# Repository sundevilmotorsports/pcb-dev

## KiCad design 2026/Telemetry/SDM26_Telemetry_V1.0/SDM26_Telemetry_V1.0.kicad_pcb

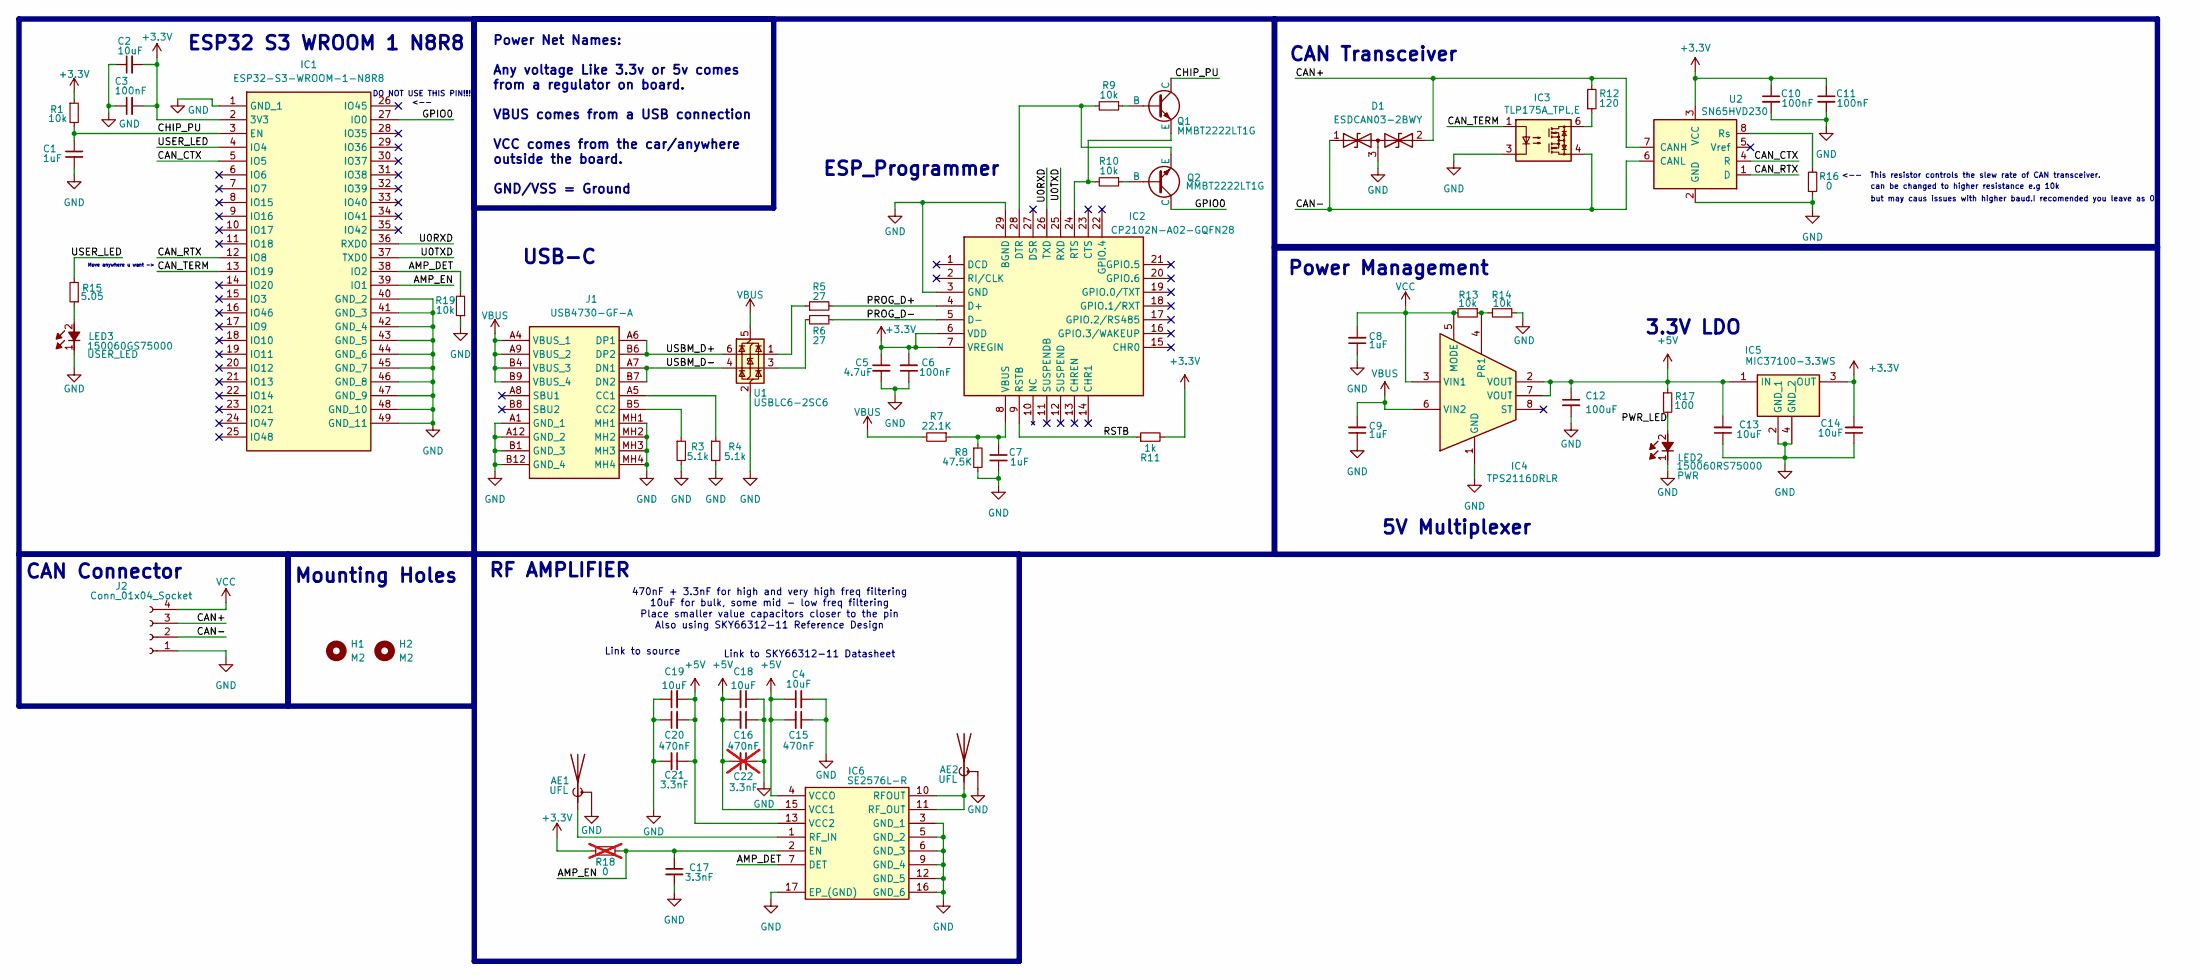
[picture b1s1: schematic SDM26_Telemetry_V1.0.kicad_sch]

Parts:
AE1, AE2: UFL; CONUFL001SMDT; Mouser Part Number N/A
C1, C7, C8, C9: 1uF; C_0603_1608Metric
C2, C4, C13, C14, C18, C19: 10uF; C_0603_1608Metric
C3, C6, C10, C11: 100nF; C_0603_1608Metric
C5: 4.7uF; C_0603_1608Metric
C12: 100uF; C_0603_1608Metric
C15, C16, C20: 470nF; C_0603_1608Metric
C17, C21: 3.3nF; C_0603_1608Metric
C22: 3.3nF; C_0603_1608Metric; not fitted
D1: ESDCAN03-2BWY; SOT65P210X110-3N; Mouser Part Number 511-ESDCAN03-2BWY
H1, H2: M2; MountingHole_2.2mm_M2
IC1: ESP32-S3-WROOM-1-N8R8; ESP32S3WROOM1UN8R8; Mouser Part Number 356-ESP32S3WRM1UN8R8
IC2: CP2102N-A02-GQFN28; QFN50P500X500X80-29N-D; Mouser Part Number 634-CP2102NA02GQFN28
IC3: TLP175A_TPL,E; TLP266J; Mouser Part Number 757-TLP175A(TPLE
IC4: TPS2116DRLR; SOTFL50P160X60-8L; Mouser Part Number 595-TPS2116DRLR
IC5: MIC37100-3.3WS; SOT230P700X180-4N; Mouser Part Number 998-MIC37100-3.3WS
IC6: SE2576L-R; QFN50P300X300X90-17L-D; Mouser Part Number 873-SE2576L-R
J1: USB4730-GF-A; USB_C_Receptacle_16P; Mouser Part Number 640-USB4730GFA
J2: Conn_01x04_Socket; JST_XH_S4B-XH-A_1x04_P2.50mm_Horizontal
LED2: 150060RS75000; LEDC1608X80N; Mouser Part Number 710-150060RS75000
LED3: 150060GS75000; LEDC1608X80N; Mouser Part Number 710-150060GS75000
Q1, Q2: MMBT2222LT1G; SOT96P237X111-3N
R1, R9, R10, R13, R14, R19: 10k; R_0603_1608Metric
R3, R4: 5.1k; R_0603_1608Metric
R5, R6: 27; R_0603_1608Metric
R7: 22.1K; R_0603_1608Metric
R8: 47.5K; R_0603_1608Metric
R11: 1k; R_0603_1608Metric
R12: 120; R_0603_1608Metric
R15: 5.05; R_0603_1608Metric
R16: 0; R_0603_1608Metric
R17: 100; R_0603_1608Metric
R18: 0; R_0603_1608Metric; not fitted
U1: USBLC6-2SC6; SOT-23-6
U2: SN65HVD230; SOIC-8_3.9x4.9mm_P1.27mm

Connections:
+3.3V: C2.2, C3.2, C5.1, C6.2, C10.1, C11.1, C14.2, IC1.2 (3V3), IC2.6 (VDD), IC2.7 (VREGIN), IC5.3 (OUT), R1.1, R11.2, R18.1, U2.3 (VCC)
+5V: C4.1, C12.1, C13.2, C15.2, C16.2, C18.2, C19.2, C20.2, C21.1, C22.2, IC4.2 (VOUT), IC4.7 (VOUT), IC5.1 (IN), IC6.4 (VCCO), IC6.13 (VCC2), IC6.15 (VCC1), R17.1
/AMP_DET: IC1.38 (IO2), IC6.7 (DET), R19.2
/AMP_EN: C17.1, IC1.39 (IO1), IC6.2 (EN), R18.2
/CAN+: D1.2, J2.3, R12.2, U2.7 (CANH)
/CAN-: D1.1, IC3.4, J2.2, U2.6 (CANL)
/CAN_CTX: IC1.5 (IO5), U2.4 (R)
/CAN_RTX: IC1.12 (IO8), U2.1 (D)
/CAN_TERM: IC1.13 (IO19), IC3.1
/CHIP_PU: C1.1, IC1.3 (EN), Q1.3 (C), R1.2
/GPIO0: IC1.27 (IO0), Q2.3 (C)
/PROG_D+: IC2.4 (D+), R5.2
/PROG_D-: IC2.5 (D-), R6.1
/PWR_LED: LED2.2 (A), R17.2
/RSTB: IC2.9 (RSTB), R11.1
/U0RXD: IC1.36 (RXD0), IC2.26 (TXD)
/U0TXD: IC1.37 (TXD0), IC2.25 (RXD)
/USBM_D+: J1.A6 (DP1), J1.B6 (DP2), U1.6 (I/O1)
/USBM_D-: J1.A7 (DN1), J1.B7 (DN2), U1.4 (I/O2)
/USER_LED: IC1.4 (IO4), R15.2
GND: AE1.2 (Shield), AE1.3 (Shield), AE2.2 (Shield), AE2.3 (Shield), C1.2, C2.1, C3.1, C4.2, C5.2, C6.1, C7.2, C8.1, C9.1, C10.2, C11.2, C12.2, C13.1, C14.1, C15.1, C16.1, C17.2, C18.1, C19.1, C20.1, C21.2, C22.1, D1.3, IC1.1 (GND_1), IC1.40 (GND_2), IC1.41 (GND_3), IC1.42 (GND_4), IC1.43 (GND_5), IC1.44 (GND_6), IC1.45 (GND_7), IC1.46 (GND_8), IC1.47 (GND_9), IC1.48 (GND_10), IC1.49 (GND_11), IC2.3 (GND), IC2.29 (BGND), IC3.3, IC4.1 (GND), IC5.2 (GND_1), IC5.4 (GND_2), IC6.3 (GND_1), IC6.5 (GND_2), IC6.6 (GND_3), IC6.9 (GND_4), IC6.12 (GND_5), IC6.16 (GND_6), IC6.17 (EP_(GND)), J1.A1 (GND_1), J1.A12 (GND_2), J1.B1 (GND_3), J1.B12 (GND_4), J1.MH1, J1.MH2, J1.MH3, J1.MH4, J2.1, LED2.1 (K), LED3.1 (K), R3.2, R4.2, R8.2, R14.1, R16.1, R19.1, U1.2 (GND), U2.2 (GND)
unnamed: AE1.1 (A), IC6.1 (RF_IN)
unnamed: AE2.1 (A), IC6.10 (RFOUT), IC6.11 (RF_OUT)
unnamed: IC2.28 (DTR), Q2.2 (E), R9.2
unnamed: IC2.24 (RTS), Q1.2 (E), R10.2
unnamed: C7.1, IC2.8 (VBUS), R7.1, R8.1
unnamed: IC3.6, R12.1
unnamed: IC4.4 (PR1), R13.1, R14.2
unnamed: J1.A5 (CC1), R4.1
unnamed: J1.B5 (CC2), R3.1
unnamed: LED3.2 (A), R15.1
unnamed: Q1.1 (B), R9.1
unnamed: Q2.1 (B), R10.1
unnamed: R5.1, U1.1 (I/O1)
unnamed: R6.2, U1.3 (I/O2)
unnamed: R16.2, U2.8 (Rs)
VBUS: C9.2, IC4.6 (VIN2), J1.A4 (VBUS_1), J1.A9 (VBUS_2), J1.B4 (VBUS_3), J1.B9 (VBUS_4), R7.2, U1.5 (VBUS)
VCC: C8.2, IC4.3 (VIN1), IC4.5 (MODE), J2.4, R13.2

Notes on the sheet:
Mounting Holes
<-- This resistor controls the slew rate of CAN transceiver.
Power Management
ESP_Programmer
RF AMPLIFIER
470nF + 3.3nF for high and very high freq filtering 10uF for bulk, some mid - low freq filtering Place smaller value capacitors closer to the pin Also using SKY66312-11 Reference Design
Power Net Names: Any voltage Like 3.3v or 5v comes from a regulator on board. VBUS comes from a USB connection VCC comes from the car/anywhere outside the board. GND/VSS = Ground
Link to source
3.3V LDO
Link to SKY66312-11 Datasheet
Move anywhere u want ->
but may caus issues with higher baud.I recomended you leave as 0.
USB-C
CAN Transceiver
5V Multiplexer
DO NOT USE THIS PIN!!! <--
can be changed to higher resistance e.g 10k
CAN Connector
ESP32 S3 WROOM 1 N8R8

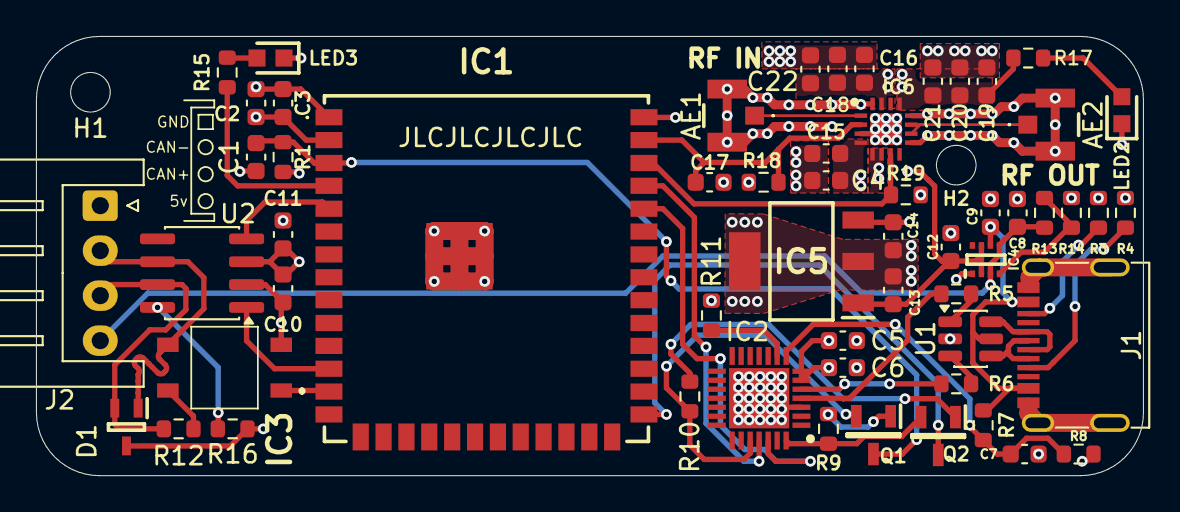
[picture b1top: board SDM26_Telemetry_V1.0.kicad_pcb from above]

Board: 4 copper layers, 61.5 x 24.4 mm, 59 parts (1 on the bottom side), 38 nets.

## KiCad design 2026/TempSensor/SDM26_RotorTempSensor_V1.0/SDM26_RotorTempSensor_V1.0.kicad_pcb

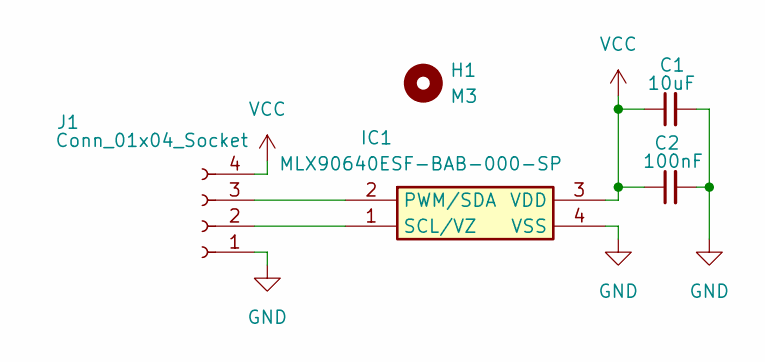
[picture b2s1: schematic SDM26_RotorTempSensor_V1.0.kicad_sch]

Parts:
C1: 10uF; C_0603_1608Metric
C2: 100nF; C_0603_1608Metric
H1: M3; MountingHole_3.2mm_M3
IC1: MLX90640ESF-BAB-000-SP; MLX90614ESFBAA000SP; Mouser Part Number 482-90614ESFBAA000SP
J1: Conn_01x04_Socket; JST_EH_B4B-EH-A_1x04_P2.50mm_Vertical

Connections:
GND: C1.2, C2.2, IC1.4 (VSS), J1.1
unnamed: IC1.2 (PWM/SDA), J1.3
unnamed: IC1.1 (SCL/VZ), J1.2
VCC: C1.1, C2.1, IC1.3 (VDD), J1.4

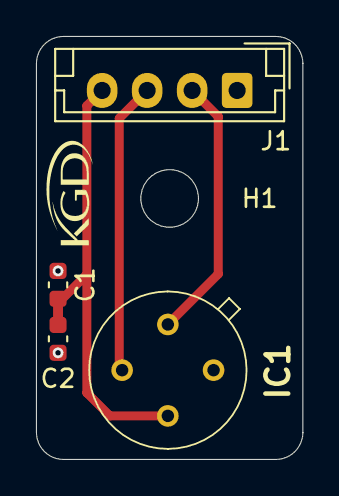
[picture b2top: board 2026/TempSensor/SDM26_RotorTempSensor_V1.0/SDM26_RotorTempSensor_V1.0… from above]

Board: 2 copper layers, 14.8 x 23.5 mm, 5 parts (0 on the bottom side), 4 nets.

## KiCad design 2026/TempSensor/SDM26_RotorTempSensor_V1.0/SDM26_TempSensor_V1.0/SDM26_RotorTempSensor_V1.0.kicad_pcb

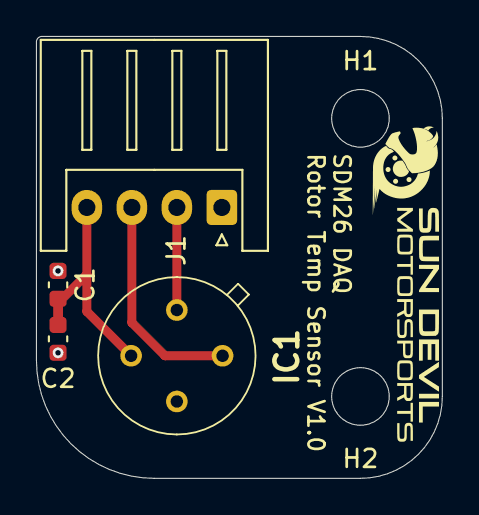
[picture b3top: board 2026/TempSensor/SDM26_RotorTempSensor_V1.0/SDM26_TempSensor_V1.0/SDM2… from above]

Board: 2 copper layers, 22.5 x 24.5 mm, 6 parts (0 on the bottom side), 4 nets.

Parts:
C1: 10uF; C_0603_1608Metric
C2: 100nF; C_0603_1608Metric
H1, H2: M3; MountingHole_3.2mm_M3
IC1: MLX90640ESF-BAB-000-SP; MLX90614ESFBAA000SP
J1: Conn_01x04_Socket; JST_XH_S4B-XH-A_1x04_P2.50mm_Horizontal

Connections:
GND: C1.2, C2.2, IC1.3 (GND), J1.1
unnamed: IC1.4 (SCL), J1.3
unnamed: IC1.1 (SDA), J1.2
VCC: C1.1, C2.1, IC1.2 (VDD), J1.4

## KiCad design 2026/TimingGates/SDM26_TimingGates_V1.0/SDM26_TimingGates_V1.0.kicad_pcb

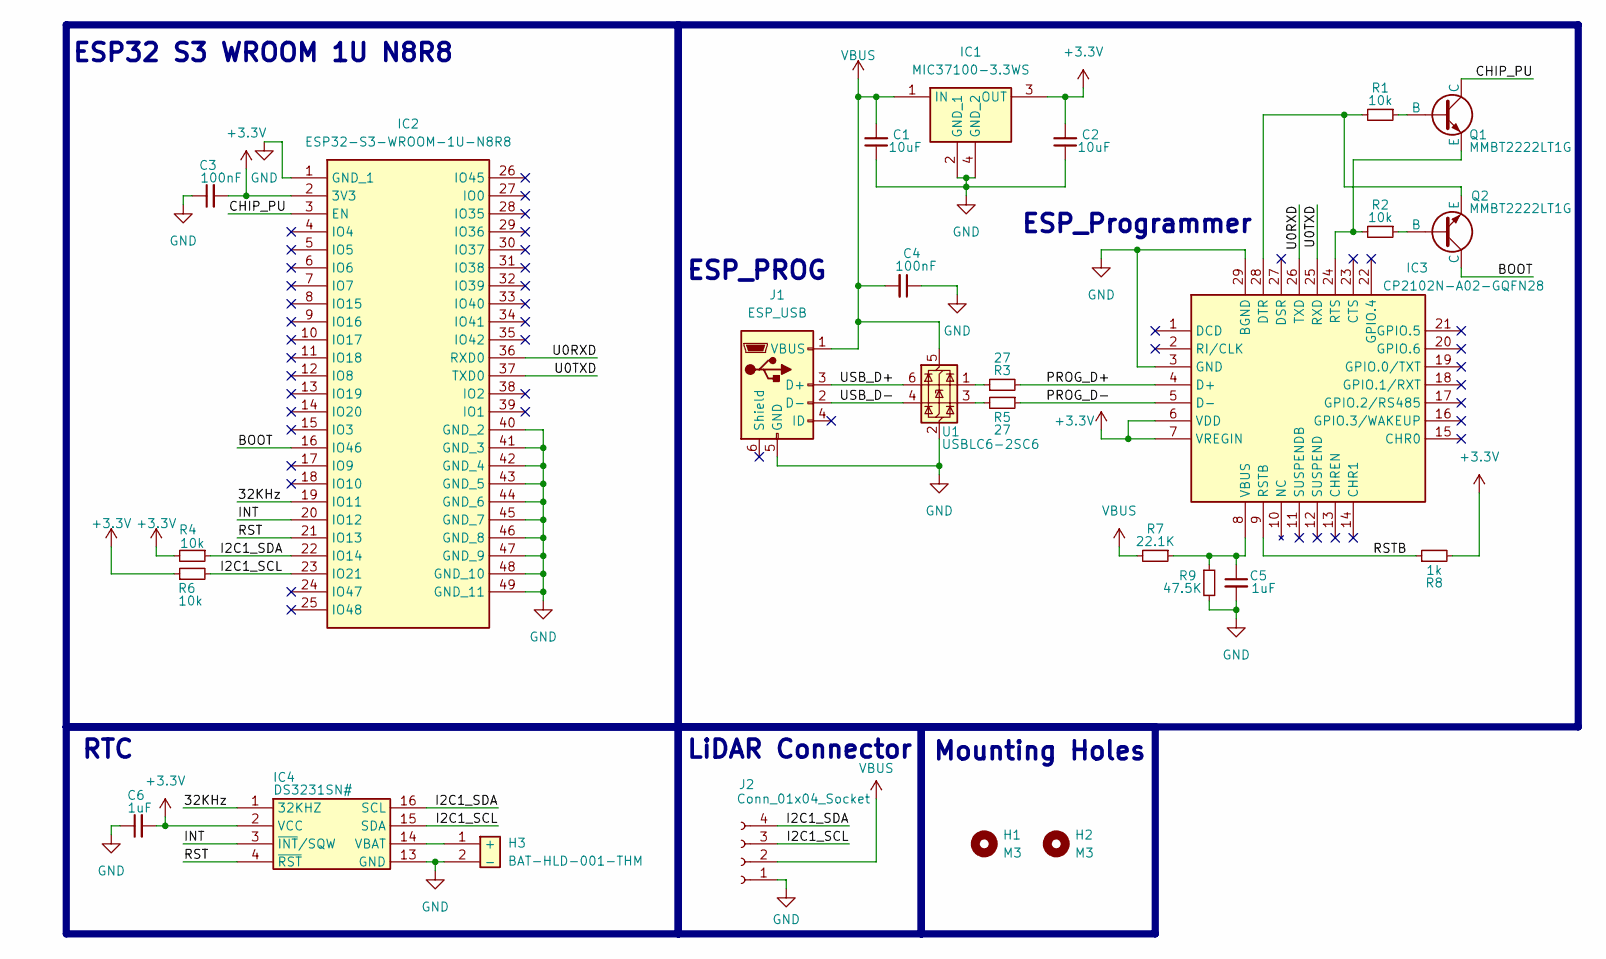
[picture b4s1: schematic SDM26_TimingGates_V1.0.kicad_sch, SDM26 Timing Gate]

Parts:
C1, C2: 10uF; C_0603_1608Metric
C3, C4: 100nF; C_0603_1608Metric
C5, C6: 1uF; C_0603_1608Metric
H1, H2: M3; MountingHole_3.2mm_M3
H3: BAT-HLD-001-THM; BATHLD001THM; Mouser Part Number N/A
IC1: MIC37100-3.3WS; SOT230P700X180-4N; Mouser Part Number 998-MIC37100-3.3WS
IC2: ESP32-S3-WROOM-1U-N8R8; ESP32S3WROOM1UN8R8; Mouser Part Number 356-ESP32S3WRM1UN8R8
IC3: CP2102N-A02-GQFN28; QFN50P500X500X80-29N-D; Mouser Part Number 634-CP2102NA02GQFN28
IC4: DS3231SN#; SOIC127P1032X265-16L; Mouser Part Number 700-DS3231SN#
J1: ESP_USB; USB_Micro-B_Molex-105017-0001
J2: Conn_01x04_Socket; JST_XH_B4B-XH-A_1x04_P2.50mm_Vertical
Q1, Q2: MMBT2222LT1G; SOT96P237X111-3N
R1, R2, R4, R6: 10k; R_0603_1608Metric
R3, R5: 27; R_0603_1608Metric
R7: 22.1K; R_0603_1608Metric
R8: 1k; R_0603_1608Metric
R9: 47.5K; R_0603_1608Metric
U1: USBLC6-2SC6; SOT-23-6

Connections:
+3.3V: C2.2, C3.2, C6.2, IC1.3 (OUT), IC2.2 (3V3), IC3.6 (VDD), IC3.7 (VREGIN), IC4.2 (VCC), R4.2, R6.1, R8.2
/32KHz: IC2.19 (IO11), IC4.1 (32KHZ)
/BOOT: IC2.16 (IO46), Q2.1 (C)
/CHIP_PU: IC2.3 (EN), Q1.1 (C)
/I2C1_SCL: IC2.23 (IO21), IC4.15 (SDA), J2.3, R6.2
/I2C1_SDA: IC2.22 (IO14), IC4.16 (SCL), J2.4, R4.1
/INT: IC2.20 (IO12), IC4.3 (~INT/SQW)
/PROG_D+: IC3.4 (D+), R3.2
/PROG_D-: IC3.5 (D-), R5.1
/RST: IC2.21 (IO13), IC4.4 (~RST)
/RSTB: IC3.9 (RSTB), R8.1
/U0RXD: IC2.36 (RXD0), IC3.26 (TXD)
/U0TXD: IC2.37 (TXD0), IC3.25 (RXD)
/USB_D+: J1.3 (D+), U1.6 (I/O1)
/USB_D-: J1.2 (D-), U1.4 (I/O2)
GND: C1.1, C2.1, C3.1, C4.1, C5.2, C6.1, H3.2 (-), IC1.2 (GND_1), IC1.4 (GND_2), IC2.1 (GND_1), IC2.40 (GND_2), IC2.41 (GND_3), IC2.42 (GND_4), IC2.43 (GND_5), IC2.44 (GND_6), IC2.45 (GND_7), IC2.46 (GND_8), IC2.47 (GND_9), IC2.48 (GND_10), IC2.49 (GND_11), IC3.3 (GND), IC3.29 (BGND), IC4.13 (GND), J1.5 (GND), J2.1, R9.2, U1.2 (GND)
unnamed: H3.1 (+), IC4.14 (VBAT)
unnamed: IC3.28 (DTR), Q2.3 (E), R1.2
unnamed: IC3.24 (RTS), Q1.3 (E), R2.2
unnamed: C5.1, IC3.8 (VBUS), R7.1, R9.1
unnamed: Q1.2 (B), R1.1
unnamed: Q2.2 (B), R2.1
unnamed: R3.1, U1.1 (I/O1)
unnamed: R5.2, U1.3 (I/O2)
VBUS: C1.2, C4.2, IC1.1 (IN), J1.1 (VBUS), J2.2, R7.2, U1.5 (VBUS)

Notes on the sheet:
ESP32 S3 WROOM 1U N8R8
RTC
ESP_PROG
Mounting Holes
ESP_Programmer
LiDAR Connector

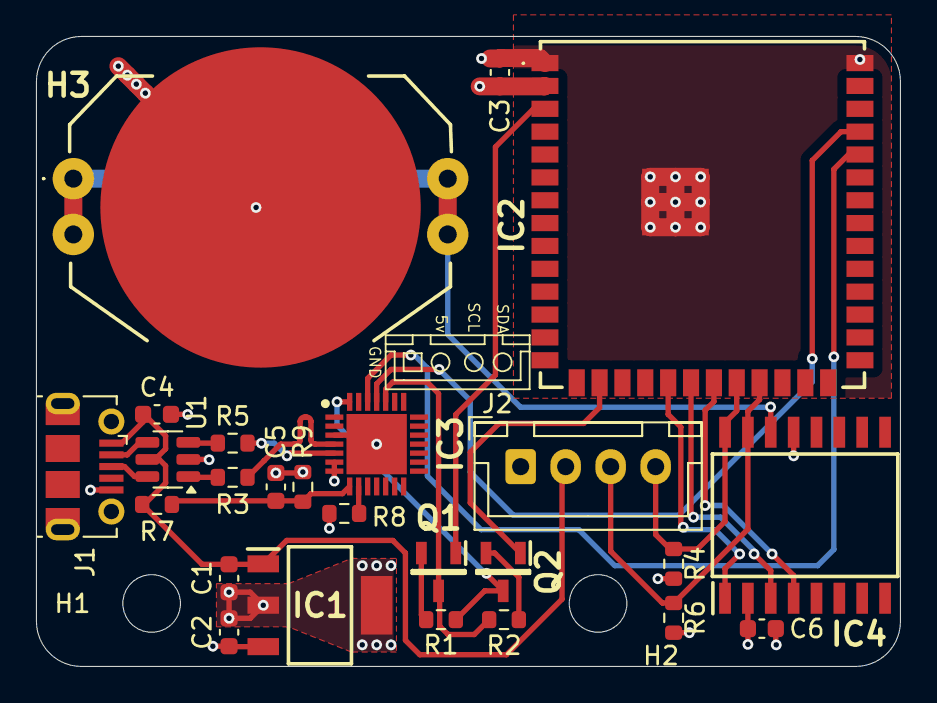
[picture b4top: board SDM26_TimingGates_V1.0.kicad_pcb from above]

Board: 4 copper layers, 48.0 x 35.0 mm, 27 parts (0 on the bottom side), 25 nets.

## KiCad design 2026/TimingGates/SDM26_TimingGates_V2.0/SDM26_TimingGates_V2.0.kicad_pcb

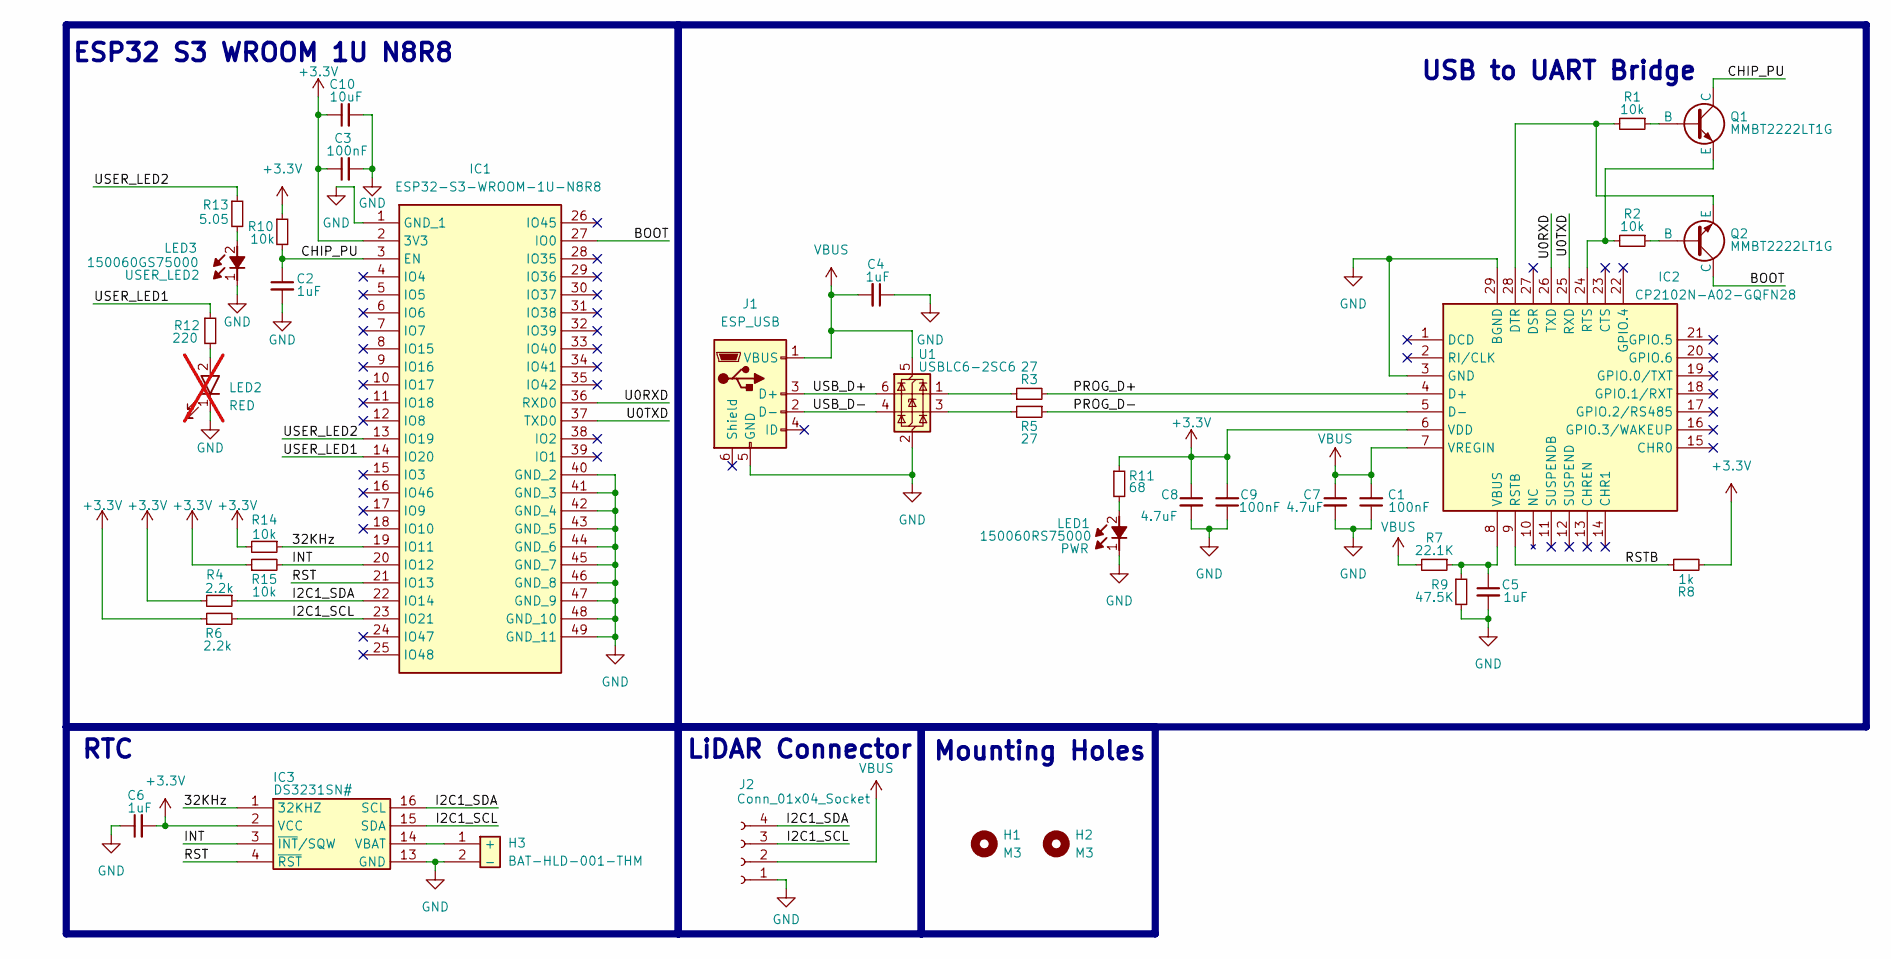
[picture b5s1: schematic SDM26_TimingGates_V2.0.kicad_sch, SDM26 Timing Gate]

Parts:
C1, C3, C9: 100nF; C_0603_1608Metric
C2, C4, C5, C6: 1uF; C_0603_1608Metric
C7, C8: 4.7uF; C_0603_1608Metric
C10: 10uF; C_0603_1608Metric
H1, H2: M3; MountingHole_3.2mm_M3
H3: BAT-HLD-001-THM; BATHLD001THM; Mouser Part Number N/A
IC1: ESP32-S3-WROOM-1U-N8R8; ESP32S3WROOM1UN8R8; Mouser Part Number 356-ESP32S3WRM1UN8R8
IC2: CP2102N-A02-GQFN28; QFN50P500X500X80-29N-D; Mouser Part Number 634-CP2102NA02GQFN28
IC3: DS3231SN#; SOIC127P1032X265-16L; Mouser Part Number 700-DS3231SN#
J1: ESP_USB; USB_Micro-B_Molex-105017-0001
J2: Conn_01x04_Socket; JST_XH_B4B-XH-A_1x04_P2.50mm_Vertical
LED1: 150060RS75000; LEDC1608X80N; Mouser Part Number 710-150060RS75000
LED2: RED; SSFLXH100LID01; Mouser Part Number 696-SSFLXH100LID01; not fitted
LED3: 150060GS75000; LEDC1608X80N; Mouser Part Number 710-150060GS75000
Q1, Q2: MMBT2222LT1G; SOT96P237X111-3N
R1, R2, R10, R14, R15: 10k; R_0603_1608Metric
R3, R5: 27; R_0603_1608Metric
R4, R6: 2.2k; R_0603_1608Metric
R7: 22.1K; R_0603_1608Metric
R8: 1k; R_0603_1608Metric
R9: 47.5K; R_0603_1608Metric
R11: 68; R_0603_1608Metric
R12: 220; R_0603_1608Metric
R13: 5.05; R_0603_1608Metric
U1: USBLC6-2SC6; SOT-23-6

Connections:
+3.3V: C3.1, C6.2, C8.1, C9.2, C10.1, IC1.2 (3V3), IC2.6 (VDD), IC3.2 (VCC), R4.2, R6.1, R8.2, R10.1, R11.1, R14.2, R15.1
/32KHz: IC1.19 (IO11), IC3.1 (32KHZ), R14.1
/BOOT: IC1.27 (IO0), Q2.3 (C)
/CHIP_PU: C2.1, IC1.3 (EN), Q1.3 (C), R10.2
/I2C1_SCL: IC1.23 (IO21), IC3.15 (SDA), J2.3, R6.2
/I2C1_SDA: IC1.22 (IO14), IC3.16 (SCL), J2.4, R4.1
/INT: IC1.20 (IO12), IC3.3 (~INT/SQW), R15.2
/PROG_D+: IC2.4 (D+), R3.2
/PROG_D-: IC2.5 (D-), R5.1
/RST: IC1.21 (IO13), IC3.4 (~RST)
/RSTB: IC2.9 (RSTB), R8.1
/U0RXD: IC1.36 (RXD0), IC2.26 (TXD)
/U0TXD: IC1.37 (TXD0), IC2.25 (RXD)
/USB_D+: J1.3 (D+), U1.6 (I/O1)
/USB_D-: J1.2 (D-), U1.4 (I/O2)
/USER_LED1: IC1.14 (IO20), R12.1
/USER_LED2: IC1.13 (IO19), R13.1
GND: C1.1, C2.2, C3.2, C4.1, C5.2, C6.1, C7.2, C8.2, C9.1, C10.2, H3.2 (-), IC1.1 (GND_1), IC1.40 (GND_2), IC1.41 (GND_3), IC1.42 (GND_4), IC1.43 (GND_5), IC1.44 (GND_6), IC1.45 (GND_7), IC1.46 (GND_8), IC1.47 (GND_9), IC1.48 (GND_10), IC1.49 (GND_11), IC2.3 (GND), IC2.29 (BGND), IC3.13 (GND), J1.5 (GND), J2.1, LED1.1 (K), LED2.1 (K), LED3.1 (K), R9.2, U1.2 (GND)
unnamed: H3.1 (+), IC3.14 (VBAT)
unnamed: IC2.28 (DTR), Q2.2 (E), R1.2
unnamed: IC2.24 (RTS), Q1.2 (E), R2.2
unnamed: C5.1, IC2.8 (VBUS), R7.1, R9.1
unnamed: LED1.2 (A), R11.2
unnamed: LED2.2 (A), R12.2
unnamed: LED3.2 (A), R13.2
unnamed: Q1.1 (B), R1.1
unnamed: Q2.1 (B), R2.1
unnamed: R3.1, U1.1 (I/O1)
unnamed: R5.2, U1.3 (I/O2)
VBUS: C1.2, C4.2, C7.1, IC2.7 (VREGIN), J1.1 (VBUS), J2.2, R7.2, U1.5 (VBUS)

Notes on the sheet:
ESP32 S3 WROOM 1U N8R8
RTC
USB to UART Bridge
Mounting Holes
LiDAR Connector

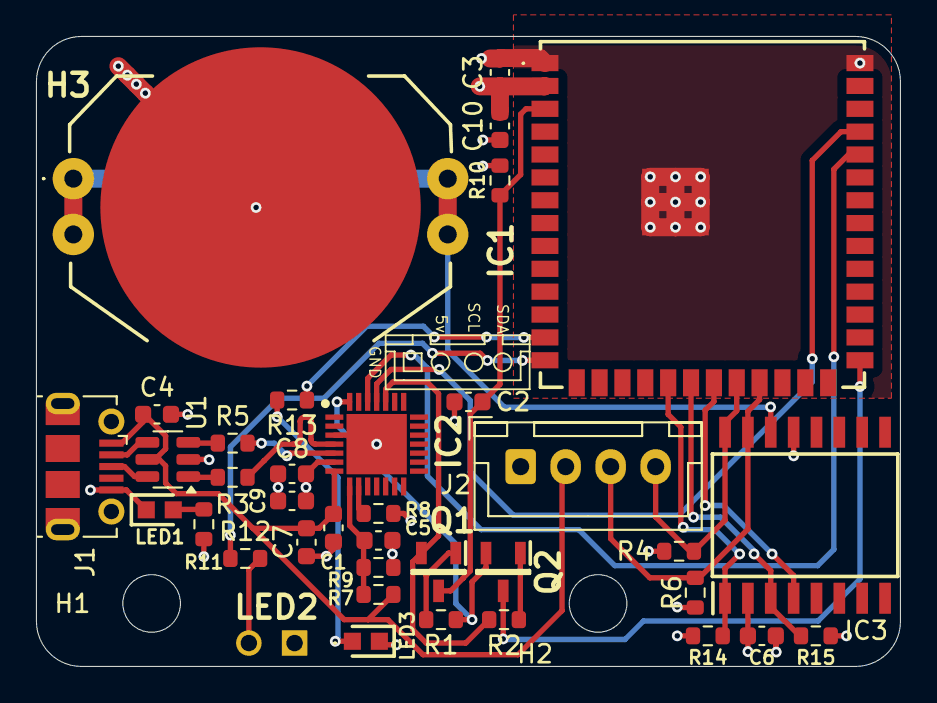
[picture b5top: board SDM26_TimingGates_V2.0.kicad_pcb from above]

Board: 4 copper layers, 48.0 x 35.0 mm, 39 parts (0 on the bottom side), 30 nets.

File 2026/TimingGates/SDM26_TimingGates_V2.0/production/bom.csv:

Designator,Footprint,Quantity,Value,LCSC Part #
"C1, C3, C9",0603,3,100nF,
C10,0603,1,10uF,
"C2, C4, C5, C6",0603,4,1uF,
"C7, C8",0603,2,4.7uF,
"H1, H2",MountingHole_3.2mm_M3,2,M3,
H3,BATHLD001THM,1,BAT-HLD-001-THM,
IC1,ESP32S3WROOM1UN8R8,1,ESP32-S3-WROOM-1U-N8R8,
IC2,QFN50P500X500X80-29N-D,1,CP2102N-A02-GQFN28,
IC3,SOIC127P1032X265-16L,1,DS3231SN#,
J1,USB_Micro-B_Molex-105017-0001,1,ESP_USB,
J2,JST_XH_B4B-XH-A_1x04_P2.50mm_Vertical,1,Conn_01x04_Socket,
LED1,LEDC1608X80N,1,150060RS75000,
LED2,SSFLXH100LID01,1,RED,
LED3,LEDC1608X80N,1,150060GS75000,
"Q1, Q2",SOT96P237X111-3N,2,MMBT2222LT1G,
"R1, R10, R14, R15, R2",0603,5,10k,
R11,0603,1,68,
R12,0603,1,220,
R13,0603,1,5.05,
"R3, R5",0603,2,27,
"R4, R6",0603,2,2.2k,
R7,0603,1,22.1K,
R8,0603,1,1k,
R9,0603,1,47.5K,
U1,SOT-23-6,1,USBLC6-2SC6,
